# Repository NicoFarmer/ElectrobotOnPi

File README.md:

# ElectrobotOnPi
Carte électronique pour Raspberry Pi pour robot

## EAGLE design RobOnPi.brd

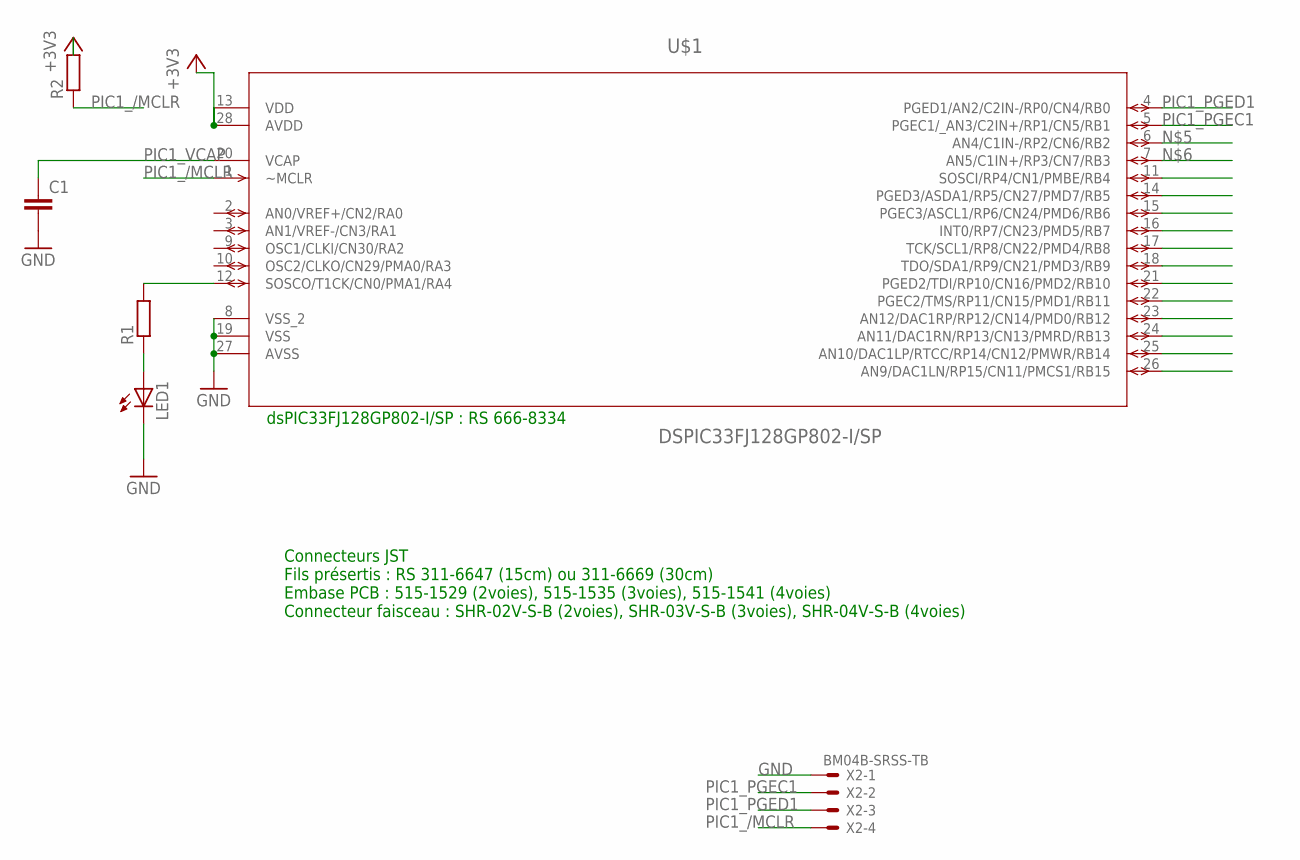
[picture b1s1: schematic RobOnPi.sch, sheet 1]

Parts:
C1: C-EUC1206; C1206
LED1: LEDSML1206; SML1206
R1, R2: R-EU_M1206; M1206
U$1: DSPIC33FJ128GP802-I/SP; DIP254P762X508-28
X2: BM04B-SRSS-TB

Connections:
+3V3: R2.2, U$1.13 (VDD), U$1.28 (AVDD)
GND: C1.2, LED1.C, U$1.8 (VSS_2), U$1.19 (VSS), U$1.27 (AVSS), X2.1
unnamed: LED1.A, R1.1
unnamed: R1.2, U$1.12 (SOSCO/T1CK/CN0/PMA1/RA4)
PIC1_/MCLR: R2.1, U$1.1 (~MCLR), X2.4
PIC1_PGEC1: U$1.5 (PGEC1/_AN3/C2IN+/RP1/CN5/RB1), X2.2
PIC1_PGED1: U$1.4 (PGED1/AN2/C2IN-/RP0/CN4/RB0), X2.3
PIC1_VCAP: C1.1, U$1.20 (VCAP)

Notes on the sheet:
Connecteurs JST Fils présertis : RS 311-6647 (15cm) ou 311-6669 (30cm) Embase PCB : 515-1529 (2voies), 515-1535 (3voies), 515-1541 (4voies) Connecteur faisceau : SHR-02V-S-B (2voies), SHR-03V-S-B (3voies), SHR-04V-S-B (4voies)
dsPIC33FJ128GP802-I/SP : RS 666-8334

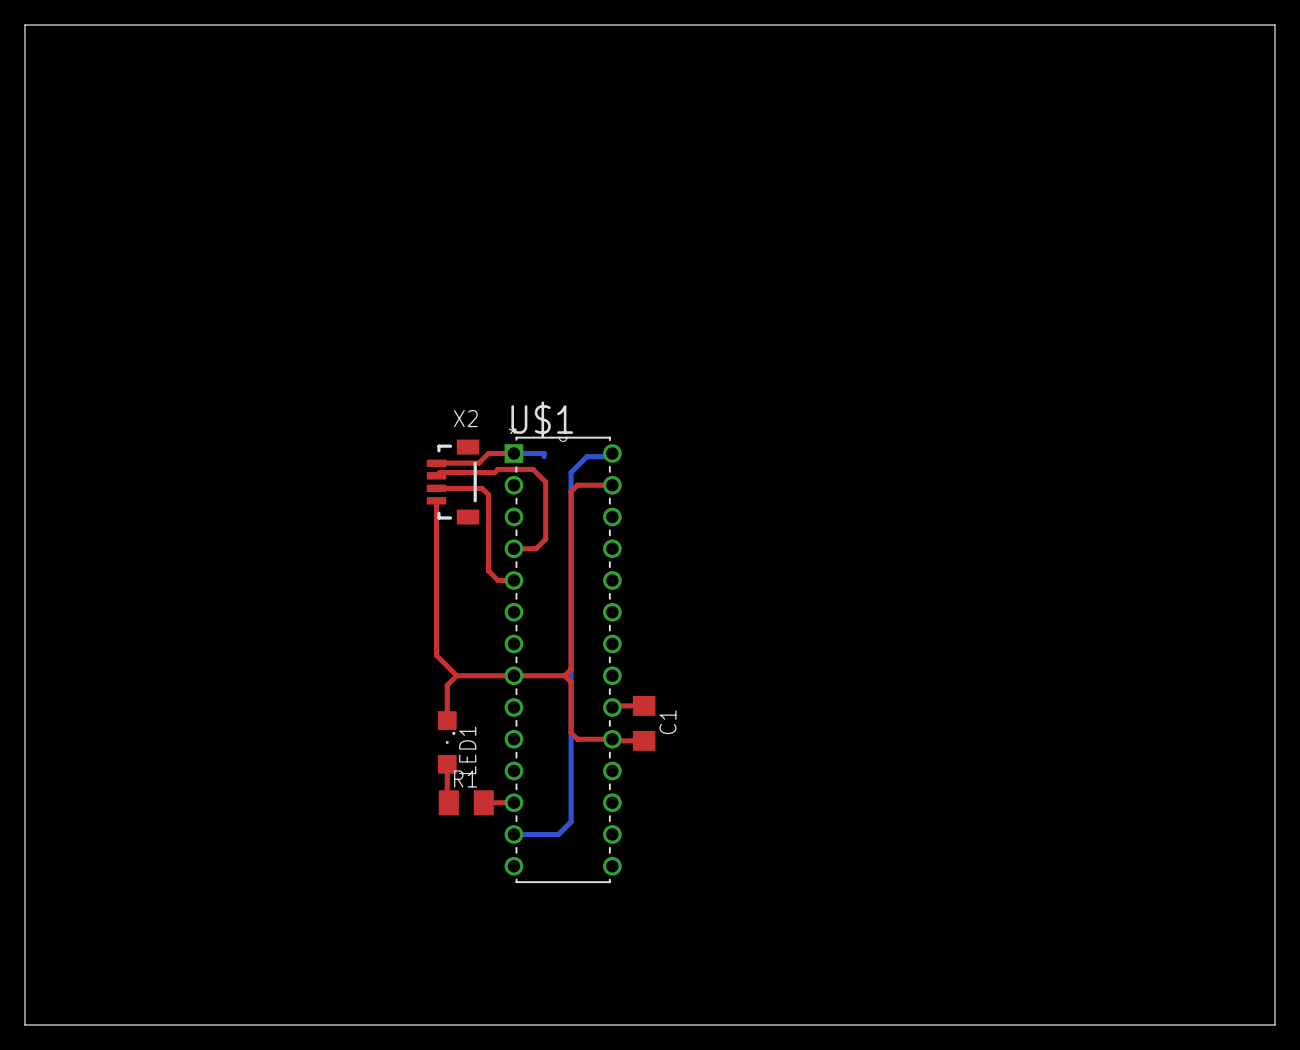
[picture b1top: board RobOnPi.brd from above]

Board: 2 copper layers, 100.0 x 80.0 mm, 6 parts (1 on the bottom side), 8 nets.

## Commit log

2018-05-01 Commit initial
2018-07-24 Create LICENSE
